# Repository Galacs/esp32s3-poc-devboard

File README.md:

# ESP32-S3 POC/Devboard

ESP32-S3 based PoC board made to test step-down power supply design, 24v level shifter, crystal circuits and RF circuit

## IC List

- ESP32-S3Fx (main MCU)
- CP2102 (USB to UART)
- TPS5430 (step-down converter)
- AP2112K & XC6206 (3v3 LDOs)
- ULN2003A (transistor array)

## Top preview

## Preview 3d render

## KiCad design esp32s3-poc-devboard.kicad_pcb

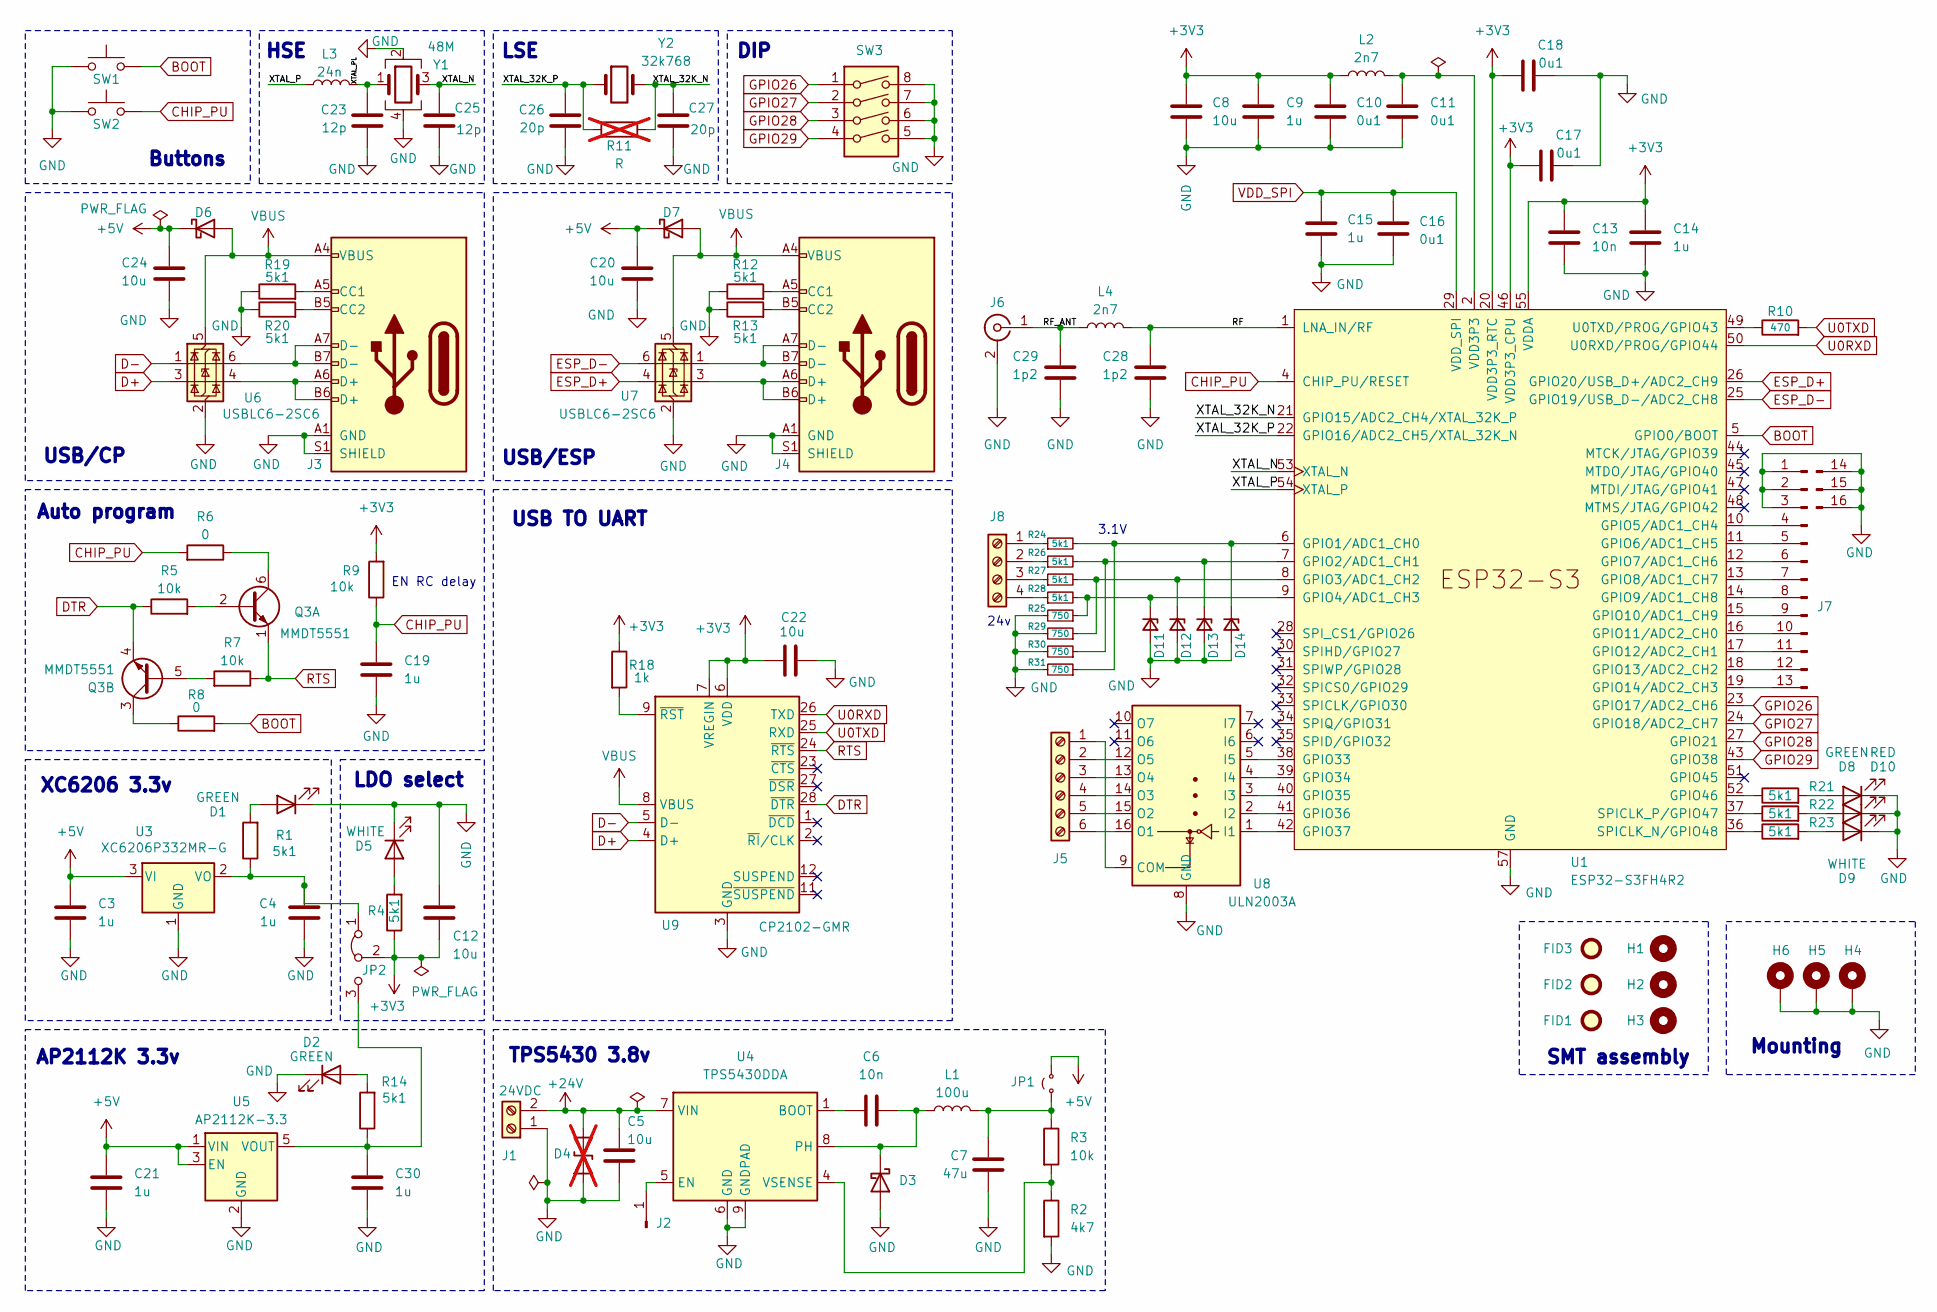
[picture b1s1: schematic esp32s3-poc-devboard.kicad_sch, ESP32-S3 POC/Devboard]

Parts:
C3, C4, C21, C30: 1u; C_0603_1608Metric; Manufacturer Part Number CL10A105KB8NNNC; JLCPCB Part # C15849
C5: 10u; C_0805_2012Metric; Manufacturer Part Number GRM21BR61H106KE43L; JLCPCB Part # C440198
C6: 10n; C_0805_2012Metric; Manufacturer Part Number CL21B103KBANNNC; JLCPCB Part # C1710
C7: 47u; C_1206_3216Metric; Manufacturer Part Number CL31A476MPHNNNE; JLCPCB Part # C96123
C8, C12, C20, C22, C24: 10u; C_0402_1005Metric; Manufacturer Part Number CL05A106MQ5NUNC; JLCPCB Part # C15525
C9, C14, C15, C19: 1u; C_0402_1005Metric; Manufacturer Part Number CL05A105KA5NQNC; JLCPCB Part # C52923
C10, C11, C16, C17, C18: 0u1; C_0402_1005Metric; Manufacturer Part Number CL05B104KB54PNC; JLCPCB Part # C307331
C13: 10n; C_0402_1005Metric; Manufacturer Part Number CL05B103KB5NNNC; JLCPCB Part # C15195
C23, C25: 12p; C_0402_1005Metric; Manufacturer Part Number 0402CG120J500NT; JLCPCB Part # C1547
C26, C27: 20p; C_0402_1005Metric; Manufacturer Part Number 0402CG200J500NT; JLCPCB Part # C1554
C28, C29: 1p2; C_0402_1005Metric; Manufacturer Part Number GJM1555C1H1R2WB01D; JLCPCB Part # C76899
D1, D2, D8: GREEN; LED_0805_2012Metric; Manufacturer Part Number KT-0805G; JLCPCB Part # C2297
D3, D6, D7: D_Schottky; D_SMA; Manufacturer Part Number SS54; JLCPCB Part # C22452
D4: D_TVS; not fitted
D5, D9: WHITE; LED_0603_1608Metric; Manufacturer Part Number KT-0603W; JLCPCB Part # C2290
D10: RED; LED_0603_1608Metric; Manufacturer Part Number KT-0603R; JLCPCB Part # C2286
D11, D12, D13, D14: BZT52B3V3; D_SOD-123; Manufacturer Part Number BZT52B3V3; JLCPCB Part # C19077392
FID1, FID2, FID3: Fiducial; Fiducial_1mm_Mask2mm
H1, H2, H3: MountingHole; ToolingHole_1.152mm
H4, H5, H6: MountingHole_Pad; MountingHole_2.2mm_M2_Pad_Via
J1: 24VDC; TerminalBlock_Altech_AK300-2_P5.00mm
J2: Conn_01x01_Pin; PinHeader_1x01_P2.54mm_Vertical
J3, J4: USB_C_Receptacle_USB2.0_14P; USB_C_Receptacle_HRO_TYPE-C-31-M-12; Manufacturer Part Number TYPE-C16PIN; JLCPCB Part # C393939
J5: Screw_Terminal_01x06; TerminalBlock_MaiXu_MX126-5.0-06P_1x06_P5.00mm
J6: Conn_Coaxial; U.FL_Hirose_U.FL-R-SMT-1_Vertical; Manufacturer Part Number U.FL-R-SMT-1(80); JLCPCB Part # C88374
J7: Conn_01x16_Pin; PinHeader_1x16_P2.54mm_Vertical
J8: Screw_Terminal_01x04; TerminalBlock_Altech_AK300-4_P5.00mm
JP1: Jumper_2_Small_Open; PinHeader_2x01_P2.54mm_Vertical
JP2: Jumper_3_Bridged12; PinHeader_1x03_P2.54mm_Vertical
L1: 100u; L_SXN_SMDRI127; Manufacturer Part Number SMDRI127-101MT; JLCPCB Part # C10150
L2, L4: 2n7; L_0402_1005Metric; Manufacturer Part Number LQW15AN2N7G80D; JLCPCB Part # C412269
L3: 24n; L_0402_1005Metric; Manufacturer Part Number LQW15AN24NG00D; JLCPCB Part # C167472
Q3: MMDT5551; SOT-363_SC-70-6; Manufacturer Part Number MMDT5551; JLCPCB Part # C41375116
R1, R4, R12, R13, R14, R19, R20, R21, R22, R23, R24, R26, R27, R28: 5k1; R_0603_1608Metric; Manufacturer Part Number 0603WAF5101T5E; JLCPCB Part # C23186
R2: 4k7; R_0603_1608Metric; Manufacturer Part Number 0603WAF4701T5E; JLCPCB Part # C23162
R3, R5, R7, R9: 10k; R_0603_1608Metric; Manufacturer Part Number 0603WAF1002T5E; JLCPCB Part # C25804
R6, R8: 0; R_0603_1608Metric; Manufacturer Part Number 0603WAF0000T5E; JLCPCB Part # C21189
R10: 470; R_0603_1608Metric; Manufacturer Part Number 0603WAF4700T5E; JLCPCB Part # C23179
R11: R; R_0603_1608Metric; not fitted
R18: 1k; R_0603_1608Metric; Manufacturer Part Number 0603WAF1001T5E; JLCPCB Part # C21190
R25, R29, R30, R31: 750; R_0603_1608Metric; Manufacturer Part Number 0603WAF7500T5E; JLCPCB Part # C23241
SW1, SW2: SW_Push; SW_SPST_Omron_B3F-40xx
SW3: SW_DIP_x04; SW_DIP_SPSTx04_Slide_9.78x12.34mm_W7.62mm_P2.54mm
U1: ESP32-S3FH4R2; QFN-56-1EP_7x7mm_P0.4mm_EP5.6x5.6mm; Manufacturer Part Number ESP32-S3FH4R2; JLCPCB Part # C3013940
U3: XC6206P332MR-G; SOT-23-3; Manufacturer Part Number XC6206P332MR-G; JLCPCB Part # C5446
U4: TPS5430DDA; TI_SO-PowerPAD-8_ThermalVias; Manufacturer Part Number TPS5430DDAR; JLCPCB Part # C9864
U5: AP2112K-3.3; SOT-23-5; Manufacturer Part Number AP2112K-3.3TRG1; JLCPCB Part # C51118
U6, U7: USBLC6-2SC6; SOT-23-6; Manufacturer Part Number USBLC6-2SC6; JLCPCB Part # C7519
U8: ULN2003A; SOIC-16_3.9x9.9mm_P1.27mm; Manufacturer Part Number ULN2003ADR; JLCPCB Part # C7512
U9: CP2102-GMR; QFN-28-1EP_5x5mm_P0.5mm_EP3.35x3.35mm; Manufacturer Part Number CP2102-GMR; JLCPCB Part # C6568
Y1: 48M; Crystal_SMD_2016-4Pin_2.0x1.6mm; Manufacturer Part Number R940000096; JLCPCB Part # C7206306
Y2: 32k768; Crystal_SMD_3215-2Pin_3.2x1.5mm; Manufacturer Part Number Q13FC13500004; JLCPCB Part # C32346

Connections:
+3V3: C8.1, C9.1, C10.1, C12.2, C13.1, C14.1, C17.1, C18.1, C22.2, JP2.2 (C), L2.1, R4.1, R9.2, R18.1, U1.20 (VDD3P3_RTC), U1.46 (VDD3P3_CPU), U1.55 (VDDA), U1.56 (VDDA), U9.6 (VDD), U9.7 (VREGIN)
+5V: C3.1, C20.1, C21.1, C24.1, D6.1 (K), D7.1 (K), JP1.2 (B), U3.3 (VI), U5.1 (VIN), U5.3 (EN)
+24V: C5.1, D4.2 (A2), J1.2, U4.7 (VIN)
/RF: C28.1, L4.2, U1.1 (LNA_IN/RF)
/RF_ANT: C29.1, J6.1 (In), L4.1
/XTAL_32K_N: C27.1, R11.2, U1.21 (GPIO15/ADC2_CH4/XTAL_32K_P), Y2.2
/XTAL_32K_P: C26.2, R11.1, U1.22 (GPIO16/ADC2_CH5/XTAL_32K_N), Y2.1
/XTAL_N: C25.1, U1.53 (XTAL_N), Y1.3
/XTAL_P: L3.1, U1.54 (XTAL_P)
/XTAL_PL: C23.2, L3.2, Y1.1
BOOT: R8.2, SW1.2, U1.5 (GPIO0/BOOT)
CHIP_PU: C19.1, R6.2, R9.1, SW2.2, U1.4 (CHIP_PU/RESET)
D+: U6.3 (I/O2), U9.4 (D+)
D-: U6.1 (I/O1), U9.5 (D-)
DTR: Q3.4 (E2), R5.1, U9.28 (~DTR)
ESP_D+: U1.26 (GPIO20/USB_D+/ADC2_CH9), U7.4 (I/O2)
ESP_D-: U1.25 (GPIO19/USB_D-/ADC2_CH8), U7.6 (I/O1)
GND: C3.2, C4.2, C5.2, C7.2, C8.2, C9.2, C10.2, C11.2, C12.1, C13.2, C14.2, C15.2, C16.2, C17.2, C18.2, C19.2, C20.2, C21.2, C22.1, C23.1, C24.2, C25.2, C26.1, C27.2, C28.2, C29.2, C30.2, D1.1 (K), D2.1 (K), D3.2 (A), D4.1 (A1), D5.1 (K), D8.1 (K), D9.1 (K), D10.1 (K), D11.2 (A), D12.2 (A), D13.2 (A), D14.2 (A), H4.1, H5.1, H6.1, J1.1, J3.A1 (GND), J3.A12 (GND), J3.B1 (GND), J3.B12 (GND), J3.S1 (SHIELD), J4.A1 (GND), J4.A12 (GND), J4.B1 (GND), J4.B12 (GND), J4.S1 (SHIELD), J6.2 (Ext), J7.1, J7.2, J7.3, J7.14, J7.15, J7.16, R2.2, R12.1, R13.1, R19.1, R20.1, R25.2, R29.2, R30.2, R31.2, SW1.1, SW2.1, SW3.5, SW3.6, SW3.7, SW3.8, U1.57 (GND), U3.1 (GND), U4.6 (GND), U4.9 (GNDPAD), U5.2 (GND), U6.2 (GND), U7.2 (GND), U8.8 (GND), U9.3 (GND), U9.29 (GND), Y1.2, Y1.4
GPIO26: SW3.1, U1.23 (GPIO17/ADC2_CH6)
GPIO27: SW3.2, U1.24 (GPIO18/ADC2_CH7)
GPIO28: SW3.3, U1.27 (GPIO21)
GPIO29: SW3.4, U1.43 (GPIO38)
unnamed: D1.2 (A), R1.2
unnamed: D2.2 (A), R14.2
unnamed: C6.1, D3.1 (K), L1.1, U4.8 (PH)
unnamed: D5.2 (A), R4.2
unnamed: D8.2 (A), R21.2
unnamed: D9.2 (A), R22.2
unnamed: D10.2 (A), R23.2
unnamed: D11.1 (K), R25.1, R28.2, U1.9 (GPIO4/ADC1_CH3)
unnamed: D12.1 (K), R27.2, R29.1, U1.8 (GPIO3/ADC1_CH2)
unnamed: D13.1 (K), R26.2, R30.1, U1.7 (GPIO2/ADC1_CH1)
unnamed: D14.1 (K), R24.2, R31.1, U1.6 (GPIO1/ADC1_CH0)
unnamed: J2.1, U4.5 (EN)
unnamed: J3.A5 (CC1), R19.2
unnamed: J3.B5 (CC2), R20.2
unnamed: J3.A6 (D+), J3.B6 (D+), U6.4 (I/O2)
unnamed: J3.A7 (D-), J3.B7 (D-), U6.6 (I/O1)
unnamed: J4.A5 (CC1), R12.2
unnamed: J4.B5 (CC2), R13.2
unnamed: J4.A6 (D+), J4.B6 (D+), U7.3 (I/O2)
unnamed: J4.A7 (D-), J4.B7 (D-), U7.1 (I/O1)
unnamed: J5.1, U8.9 (COM)
unnamed: J5.2, U8.12 (O5)
unnamed: J5.3, U8.13 (O4)
unnamed: J5.4, U8.14 (O3)
unnamed: J5.5, U8.15 (O2)
unnamed: J5.6, U8.16 (O1)
unnamed: J7.4, U1.10 (GPIO5/ADC1_CH4)
unnamed: J7.5, U1.11 (GPIO6/ADC1_CH5)
unnamed: J7.6, U1.12 (GPIO7/ADC1_CH6)
unnamed: J7.7, U1.13 (GPIO8/ADC1_CH7)
unnamed: J7.8, U1.14 (GPIO9/ADC1_CH8)
unnamed: J7.9, U1.15 (GPIO10/ADC1_CH9)
unnamed: J7.10, U1.16 (GPIO11/ADC2_CH0)
unnamed: J7.11, U1.17 (GPIO12/ADC2_CH1)
unnamed: J7.12, U1.18 (GPIO13/ADC2_CH2)
unnamed: J7.13, U1.19 (GPIO14/ADC2_CH3)
unnamed: J8.1, R24.1
unnamed: J8.2, R26.1
unnamed: J8.3, R27.1
unnamed: J8.4, R28.1
unnamed: C7.1, JP1.1 (A), L1.2, R3.1
unnamed: C4.1, JP2.1 (A), R1.1, U3.2 (VO)
unnamed: C30.1, JP2.3 (B), R14.1, U5.5 (VOUT)
unnamed: Q3.2 (B1), R5.2
unnamed: Q3.6 (C1), R6.1
unnamed: Q3.5 (B2), R7.2
unnamed: Q3.3 (C2), R8.1
unnamed: U1.38 (GPIO33), U8.5 (I5)
unnamed: U1.39 (GPIO34), U8.4 (I4)
unnamed: U1.40 (GPIO35), U8.3 (I3)
unnamed: U1.41 (GPIO36), U8.2 (I2)
unnamed: U1.42 (GPIO37), U8.1 (I1)
unnamed: R21.1, U1.52 (GPIO46)
unnamed: R23.1, U1.36 (SPICLK_N/GPIO48)
unnamed: R22.1, U1.37 (SPICLK_P/GPIO47)
unnamed: R10.1, U1.49 (U0TXD/PROG/GPIO43)
unnamed: C6.2, U4.1 (BOOT)
unnamed: R2.1, R3.2, U4.4 (VSENSE)
unnamed: R18.2, U9.9 (~RST)
RTS: Q3.1 (E1), R7.1, U9.24 (~RTS)
U0RXD: U1.50 (U0RXD/PROG/GPIO44), U9.26 (TXD)
U0TXD: R10.2, U9.25 (RXD)
VBUS: D6.2 (A), D7.2 (A), J3.A4 (VBUS), J3.A9 (VBUS), J3.B4 (VBUS), J3.B9 (VBUS), J4.A4 (VBUS), J4.A9 (VBUS), J4.B4 (VBUS), J4.B9 (VBUS), U6.5 (VBUS), U7.5 (VBUS), U9.8 (VBUS)
VDD3P3: C11.1, L2.2, U1.2 (VDD3P3), U1.3 (VDD3P3)
VDD_SPI: C15.1, C16.1, U1.29 (VDD_SPI)

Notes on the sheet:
AP2112K 3.3v
DIP
3.1V
HSE
EN RC delay
USB TO UART
Mounting
SMT assembly
Auto program
LSE
USB/ESP
LDO select
24v
Buttons
XC6206 3.3v
TPS5430 3.8v
USB/CP

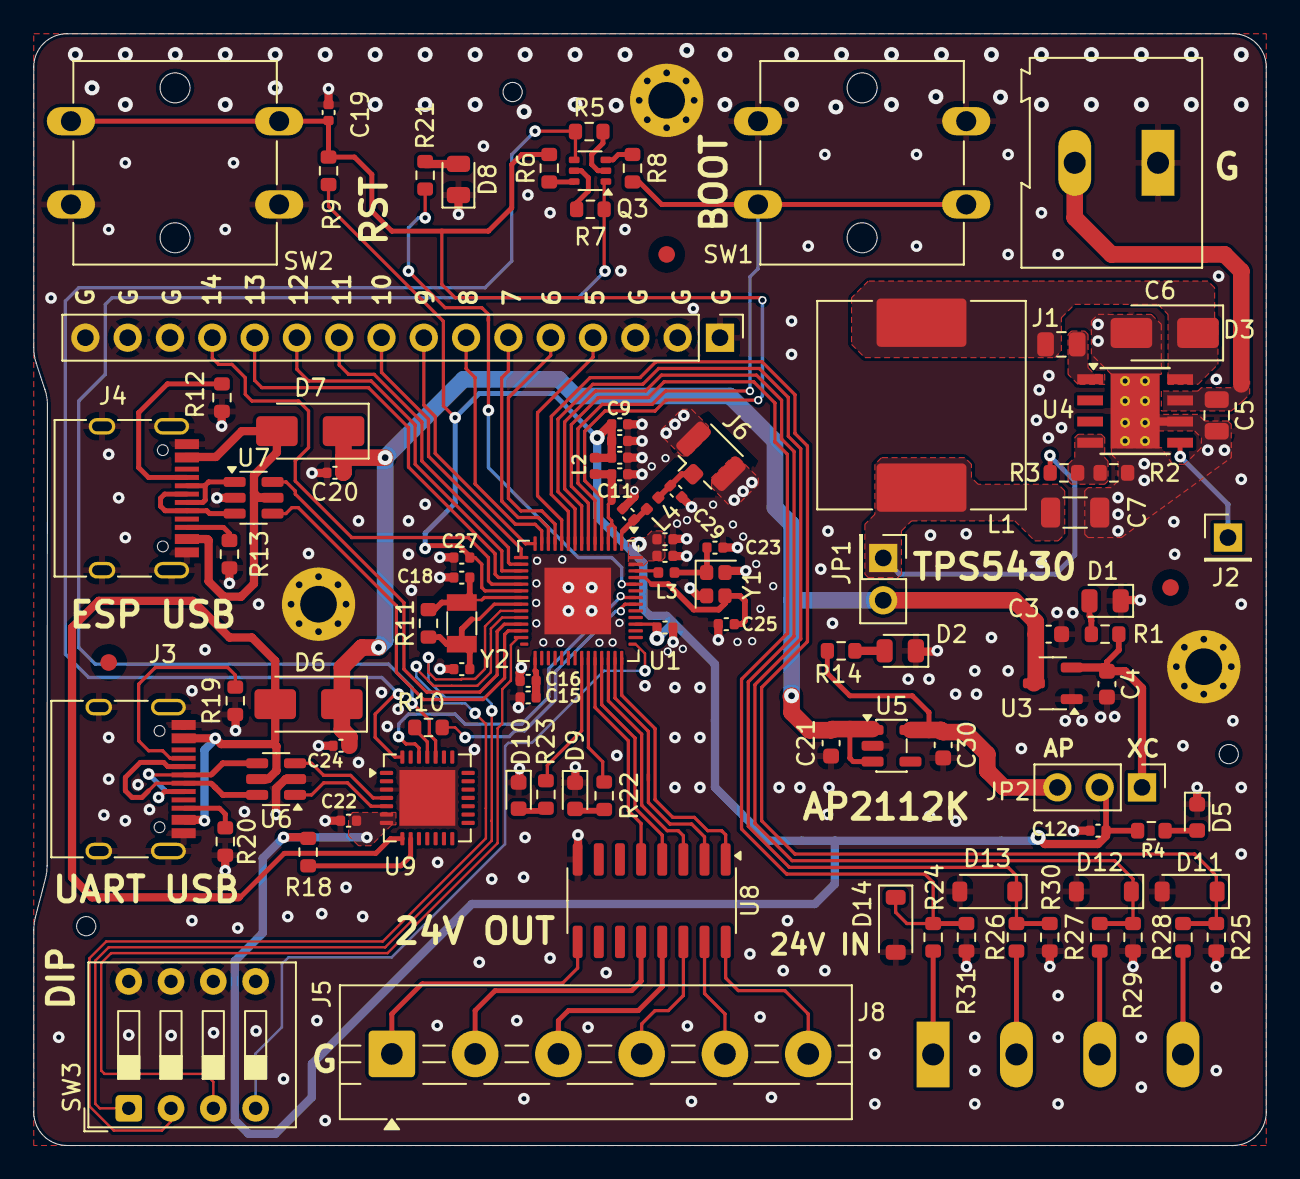
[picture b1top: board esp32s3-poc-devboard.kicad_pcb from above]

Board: 4 copper layers, 74.0 x 66.8 mm, 106 parts (0 on the bottom side), 87 nets.

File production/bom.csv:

Designator,Footprint,Quantity,Value,LCSC Part #
"C10, C11, C16, C17, C18",0402,5,0u1,C307331
"C12, C20, C22, C24, C8",0402,5,10u,C15525
C13,0402,1,10n,C15195
"C14, C15, C19, C9",0402,4,1u,C52923
"C21, C3, C30, C4",0603,4,1u,C15849
"C23, C25",0402,2,12p,C1547
"C26, C27",0402,2,20p,C1554
"C28, C29",0402,2,1p2,C76899
C5,0805,1,10u,C440198
C6,0805,1,10n,C1710
C7,1206,1,47u,C96123
"D1, D2, D8",0805,3,GREEN,C2297
D10,0603,1,RED, C2286
"D11, D12, D13, D14",D_SOD-123,4,BZT52B3V3,C19077392
"D3, D6, D7",D_SMA,3,D_Schottky,C22452
"D5, D9",0603,2,WHITE,C2290
"J3, J4",USB_C_Receptacle_HRO_TYPE-C-31-M-12,2,USB_C_Receptacle_USB2.0_14P,C393939
J6,U.FL_Hirose_U.FL-R-SMT-1_Vertical,1,Conn_Coaxial,C88374
L1,L_SXN_SMDRI127,1,100u,C10150
"L2, L4",0402,2,2n7,C412269
L3,0402,1,24n,C167472
Q3,SOT-363_SC-70-6,1,MMDT5551,C41375116
"R1, R12, R13, R14, R19, R20, R21, R22, R23, R24, R26, R27, R28, R4",0603,14,5k1,C23186
R10,0603,1,470,C23179
R18,0603,1,1k,C21190
R2,0603,1,4k7,C23162
"R25, R29, R30, R31",0603,4,750,C23241
"R3, R5, R7, R9",0603,4,10k,C25804
"R6, R8",0603,2,0,C21189
U1,QFN-56-1EP_7x7mm_P0.4mm_EP5.6x5.6mm,1,ESP32-S3FH4R2,C3013940
U3,SOT-23-3,1,XC6206P332MR-G, C5446
U4,TI_SO-PowerPAD-8_ThermalVias,1,TPS5430DDA,C9864
U5,SOT-23-5,1,AP2112K-3.3,C51118
"U6, U7",SOT-23-6,2,USBLC6-2SC6,C7519
U8,SOIC-16_3.9x9.9mm_P1.27mm,1,ULN2003A,C7512
U9,QFN-28-1EP_5x5mm_P0.5mm_EP3.35x3.35mm,1,CP2102-GMR,C6568
Y1,Crystal_SMD_2016-4Pin_2.0x1.6mm,1,48M,C7206306
Y2,Crystal_SMD_3215-2Pin_3.2x1.5mm,1,32k768,C32346

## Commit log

2025-07-16 AMS117 3.3v ldo
2025-07-16 updated AMS117 3.3v ldo
2025-07-16 add XC6206 3.3v ldo
2025-07-16 add ldo selection jumper
2025-07-16 add notes txt
2025-07-16 changed pwr header to jumper
2025-07-19 change to non-polarized capacitors
2025-07-19 remove 3v3 jumper
2025-07-19 TPS5430 3.8v smps
2025-07-19 update TPS5430 location
2025-07-20 add 3v3 power selection jumper
2025-07-20 add mcu power strapping capacitors
2025-07-20 add auto program circuit
2025-07-20 add CP2102N usb to uart
2025-07-20 add missing esp32 gnd
2025-07-20 add rst/boot buttons
2025-07-20 add vbus to avoid feeding usb from smps
2025-07-20 fix some ground symbols orientation
2025-07-20 move blocks
2025-07-20 remove unnecessary resistor on U0RXD
2025-07-22 add LSE and HSE crystals
2025-07-28 add ULN2003A transistor array
2025-07-28 fix ULN2003A orientation and add NCs
2025-08-03 add rf circuit
2025-08-03 add pin headers
2025-08-03 add noconnect to esp32s3
2025-08-03 add screw terminal input
2025-08-03 add esp32 status led
2025-08-03 add power flags for schematic erc
2025-08-03 move esp32
2025-08-11 assign footprints
2025-08-11 add screw terminal 24v to 3.1v voltage divider
2025-08-11 add dip switches
2025-08-11 add dip switch and resistor footprints
2025-08-11 remove unconnected no connect
2025-08-11 add netclasses
2025-08-11 add ordering info to BOM
2025-08-11 fix internal flash/psram pins
2025-08-11 add schematic title
2025-08-11 add pcb stackup and constraints
2025-08-12 import from schematic to pcb
2025-08-12 add or link missing 3d models
2025-08-12 fix large screw terminal 3d model height
2025-08-12 add 24V symbol and netclass
2025-08-12 add missing R11 footprint
2025-08-12 add net classes colors
2025-08-12 initial rough pcb placement
2025-08-12 pcb placement refinement
2025-08-12 refine usb diode placement
2025-08-12 reduce component spread
2025-08-12 finish initial component placement
2025-08-12 clean up silkscreen
2025-08-12 add board outline
2025-08-12 add inner ground layers
2025-08-12 add jlc tooling holes
2025-08-12 add M1 mounting holes
2025-08-12 add fiducials
2025-08-12 add ground vias
2025-08-13 add rf routing
2025-08-13 crystal routing
2025-08-13 add smps routing
2025-08-13 add uart traces routing
2025-08-13 add esp usb routing
2025-08-13 add usb to uart routing
2025-08-14 add ground return vias
2025-08-14 move leds
2025-08-14 ams117 routing
2025-08-14 xc6206 routing
2025-08-14 ldo select routing
2025-08-14 auto programming routing
2025-08-14 add pin headers routing
2025-08-14 add dip switches routing
2025-08-14 add 24v O routing
2025-08-15 add 24v I routing
2025-08-15 add status leds routing
2025-08-15 add top layer gnd pour
2025-08-15 add +3v3 pwr routing
2025-08-15 add stitching vias
2025-08-15 improve silkscreen
2025-08-15 add rf lna in test point
2025-08-15 remove unused internal pads
2025-08-15 run drc and fixes
2025-08-15 add silkscreen text & logos
2025-08-15 fix top layer gnd
2025-08-15 add ce symbol
2025-08-15 add missing +3v3 connection
2025-08-15 fix unconnected track
2025-08-15 fix various unconnected nets
2025-08-15 add production files
2025-08-15 add README.md
2025-09-06 add case freecad model
2025-12-10 schem: move 24v input to ADC pins
2025-12-10 schem: add 3v3 protection diodes to adc pins
2025-12-10 schem: update USBC symbol
2025-12-10 schem: run and fix ERC
2025-12-10 schem: update spare gpio pins
2025-12-10 pcb: add new pin organisation
2025-12-10 schem: add fiducials, mounting and tooling holes
2025-12-10 pcb: import fiducials, mounting and tooling holes
2025-12-10 pcb: run and fix DRC
2025-12-10 pcb: add missing usb 3d models
2025-12-10 pcb: place grid and drill origin
2025-12-10 rev 02
2025-12-10 pcb: fix silkscreen to reflect pin changes
2025-12-10 pcb: add stitching vias
2025-12-10 schem: replace TPS5430 Cout with basic part
2025-12-10 pcb: change usb to uart to extended CP2102-GMR
2025-12-10 pcb: update UART layout for new part
2025-12-10 schem: switched one ldo to AP2112K
2025-12-10 pcb: add AP2112K routing
2025-12-10 pcb: remove unused pads
2025-12-10 docs: update README to reflect new ics
2025-12-10 regenerate production files
